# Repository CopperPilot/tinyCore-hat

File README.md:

# TinyCore Hat Template

A starter template for creating custom hardware hats for the [TinyCore](https://mr.industries/) using CopperPilot.

## What's Included

This template provides:
- **Pin Headers**: Pre-configured connectors matching TinyCore's pinout
- **Board Outline**: Correctly sized PCB outline for a TinyCore hat
- **KiCad Project**: Ready-to-open schematic and PCB files

## Getting Started

### 1. Clone This Template

Clone the repo:

```bash
git clone https://github.com/CopperPilot/tinyCore-hat.git my-tinycore-hat
cd my-tinycore-hat
```

### 2. Open with CopperPilot

1. Launch CopperPilot
2. Open the project you just cloned
3. CopperPilot will automatically detect the KiCad project files

### 3. Start Designing with AI

CopperPilot uses AI to help you design hardware through natural conversation. Here's how:

**Chat with your schematic**: Describe what you want to build, and CopperPilot will:
- Search KiCad libraries for appropriate components
- Suggest multiple design options
- Add components to your schematic
- Wire up connections based on datasheets
- Place support components (resistors, capacitors, etc.)

**Example workflow** (based on our [walkie-talkie tutorial](https://copperpilot.ai/documentation/tutorial/walkie-talkie-hat)):

```
You: "I want to build a walkie-talkie hat using ESP-NOW protocol with a microphone and speaker"

CopperPilot: [Searches KiCad libraries and proposes options]

You: "Use option 2 with the analog mic and amplifier"

CopperPilot: [Adds components to schematic]

You: "Wire up the microphone"

CopperPilot: [Consults datasheets and creates connections]

You: "Now wire up the speaker"

CopperPilot: [Completes the speaker circuit with support components]
```

### 4. Review and Route

After CopperPilot adds components:
1. Review the proposed changes in the preview
2. Click "Accept changes" to apply them
3. Update the PCB from the schematic
4. Use a combination of auto-routing and manual routing for traces
5. Position support components as needed

### 5. Design Validation

Ask CopperPilot to review your design:

```
You: "Review my PCB design"
```

CopperPilot will identify issues like:
- Unconnected signal paths
- Missing components
- Routing problems
- Design rule violations

## Tips for Success

- **Be specific**: The more detail you provide, the better CopperPilot can help
- **Iterate**: Start simple, then add complexity
- **Review carefully**: Always check CopperPilot's suggestions before accepting
- **Use validation**: Regular design reviews catch issues early

## Example Projects

- **Walkie-Talkie Hat**: ESP-NOW communication with mic and speaker ([tutorial](https://copperpilot.ai/documentation/tutorial/walkie-talkie-hat))
- *Add your project here with a PR!*

## Need Help?

- 📚 [CopperPilot Documentation](https://copperpilot.ai/documentation)
- 💬 [Discord Community](https://discord.gg/yecEmkaGs8)

## Contributing

Found a bug or want to improve the template? Pull requests are welcome!

## License

MIT

---

**Ready to build?** Clone this template and start chatting with CopperPilot to bring your hardware ideas to life!

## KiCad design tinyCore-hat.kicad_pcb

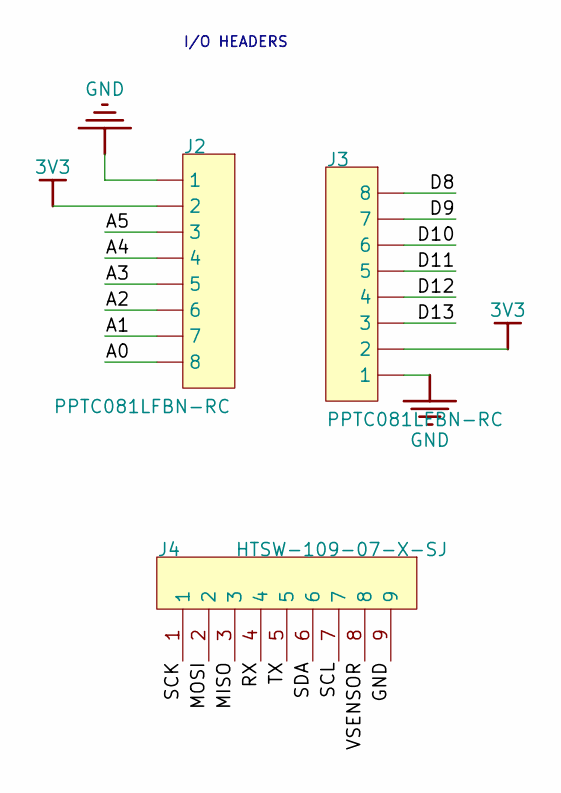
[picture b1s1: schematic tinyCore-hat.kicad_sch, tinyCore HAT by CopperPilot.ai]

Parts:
J2, J3: PPTC081LFBN-RC; 8_PIN_100MIL - Female; MFR PART # PPTC081LFBN-RC; LCSC PART# C27438
J4: HTSW-109-07-X-SJ; JM-9_HTSW-109-07-X-S; MFR PN HTSW-109-07-X-SJ; LCSC PART# C2894932

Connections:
3V3: J2.2, J3.2
/<NO NET>: J2.8
/A1: J2.7
/A2: J2.6
/A3: J2.5
/A4: J2.4
/A5: J2.3
/D8: J3.8
/D9: J3.7
/D10: J3.6
/D11: J3.5
/D12: J3.4
/D13: J3.3
/MISO: J4.3
/MOSI: J4.2
/RX: J4.4
/SCK: J4.1
/SCL: J4.7
/SDA: J4.6
/TX: J4.5
/VSENSOR: J4.8
GND: J2.1, J3.1, J4.9

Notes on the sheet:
I/O HEADERS

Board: 4 copper layers, 3 parts (0 on the bottom side), 2 nets, no tracks yet.

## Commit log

2025-11-14 init
2025-11-14 datasheet URL
2025-11-14 fix(pcb): board outline
2025-11-14 fix(pcb): gnd plane
2025-11-14 fix(pcb): text overlap
2025-11-15 docs(README.md)
2025-11-15 docs(preview)
